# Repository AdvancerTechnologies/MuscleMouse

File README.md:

Muscle-Mouse
============

Example code and files for the Muscle Mouse project

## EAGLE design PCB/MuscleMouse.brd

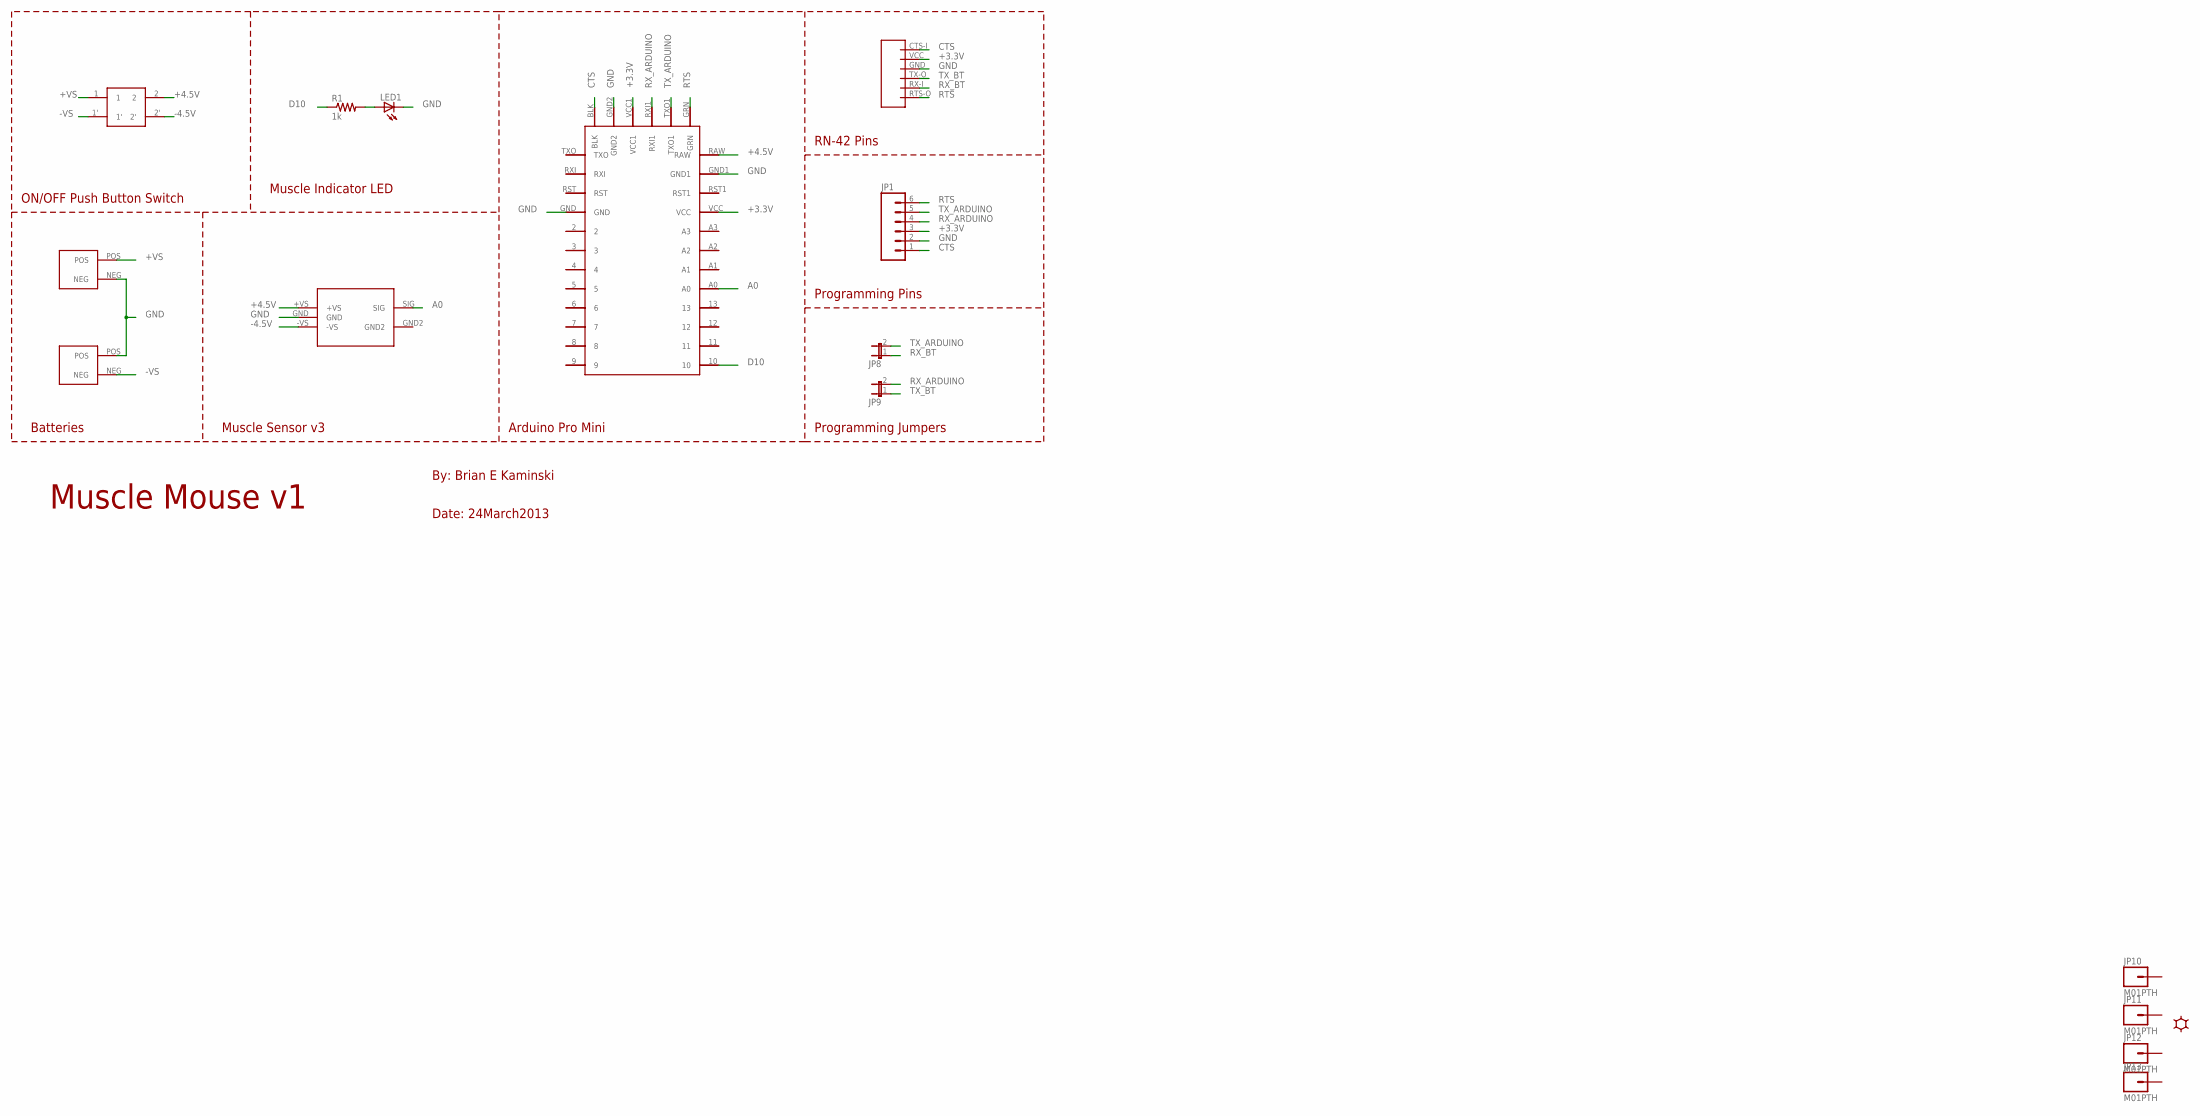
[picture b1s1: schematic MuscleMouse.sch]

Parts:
JP1: M06SIP; 1X06
JP8, JP9: JUMPER-2SMD-NC; SJ_2S
JP10, JP11, JP12, JP13: M01PTH; 1X01
LED1: LED0603; LED-0603
R1: 1k; 1206
U$1, U$2: AAA_BATT_HOLDER_3STACK
U$3: BLUESMIRF_HID
U$4: MUSCLE_SENSOR_V3
U$5: ARDUINO_PRO_MINI
U$6: ON_OFF_BUTTON
U$7: LOGOBIG; LOGO_BIG

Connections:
+3.3V: JP1.3, U$3.VCC, U$5.VCC, U$5.VCC1
+4.5V: U$4.+VS, U$5.RAW, U$6.2
+VS: U$1.POS, U$6.1
-4.5V: U$4.-VS, U$6.2'
-VS: U$2.NEG, U$6.1'
A0: U$4.SIG, U$5.A0
CTS: JP1.1, U$3.CTS-I, U$5.BLK
D10: R1.1, U$5.10
GND: JP1.2, LED1.C, U$1.NEG, U$2.POS, U$3.GND, U$4.GND, U$5.GND, U$5.GND1, U$5.GND2
unnamed: LED1.A, R1.2
RTS: JP1.6, U$3.RTS-O, U$5.GRN
RX_ARDUINO: JP1.4, JP9.2, U$5.RXI1
RX_BT: JP8.1, U$3.RX-I
TX_ARDUINO: JP1.5, JP8.2, U$5.TXO1
TX_BT: JP9.1, U$3.TX-O

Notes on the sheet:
Arduino Pro Mini
Batteries
Programming Jumpers
Muscle Sensor v3
ON/OFF Push Button Switch
Muscle Indicator LED
Programming Pins
RN-42 Pins
Muscle Mouse v1
By: Brian E Kaminski
Date: 24March2013

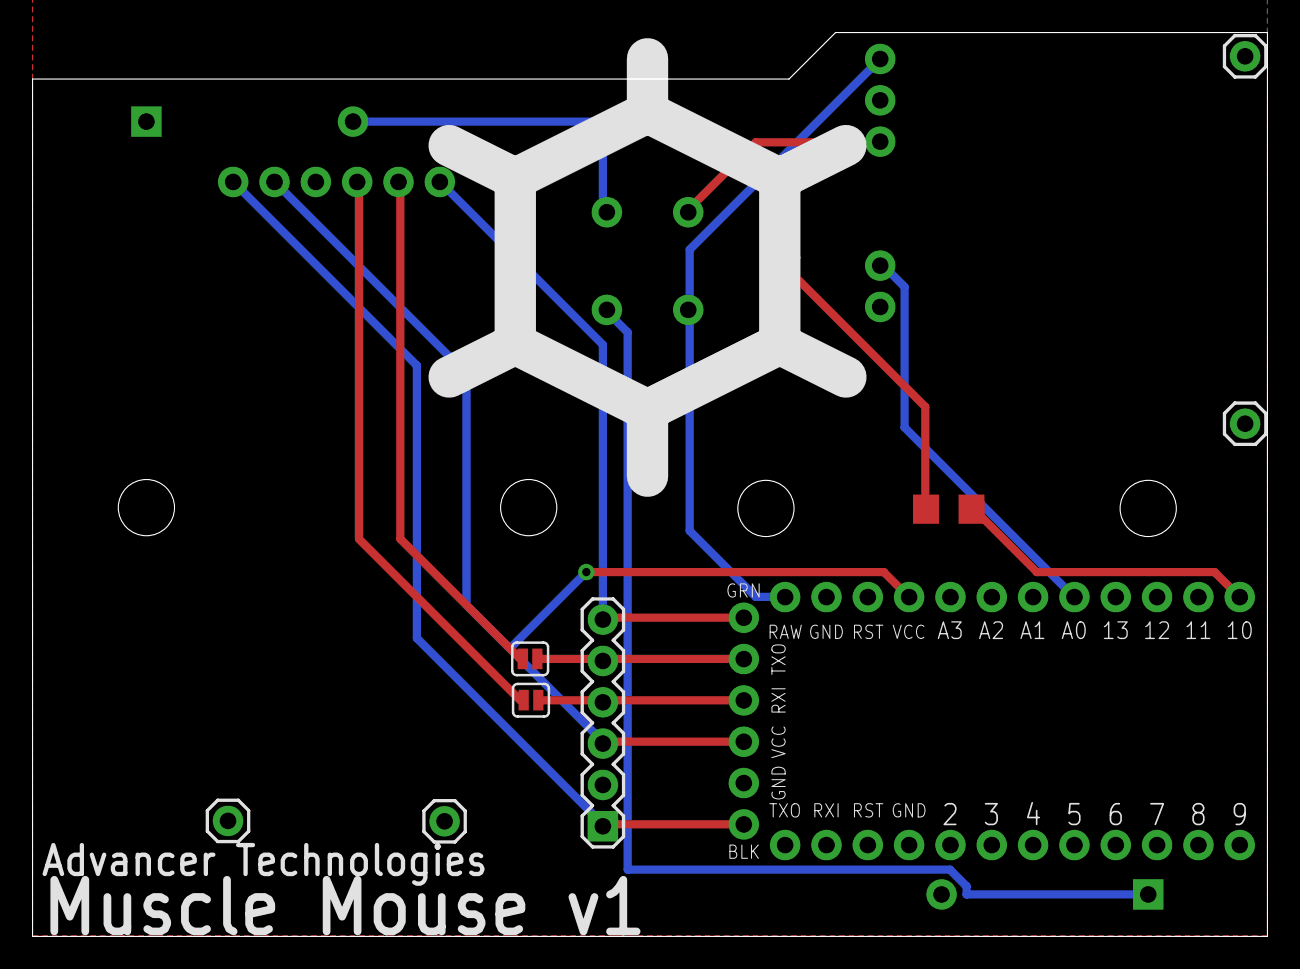
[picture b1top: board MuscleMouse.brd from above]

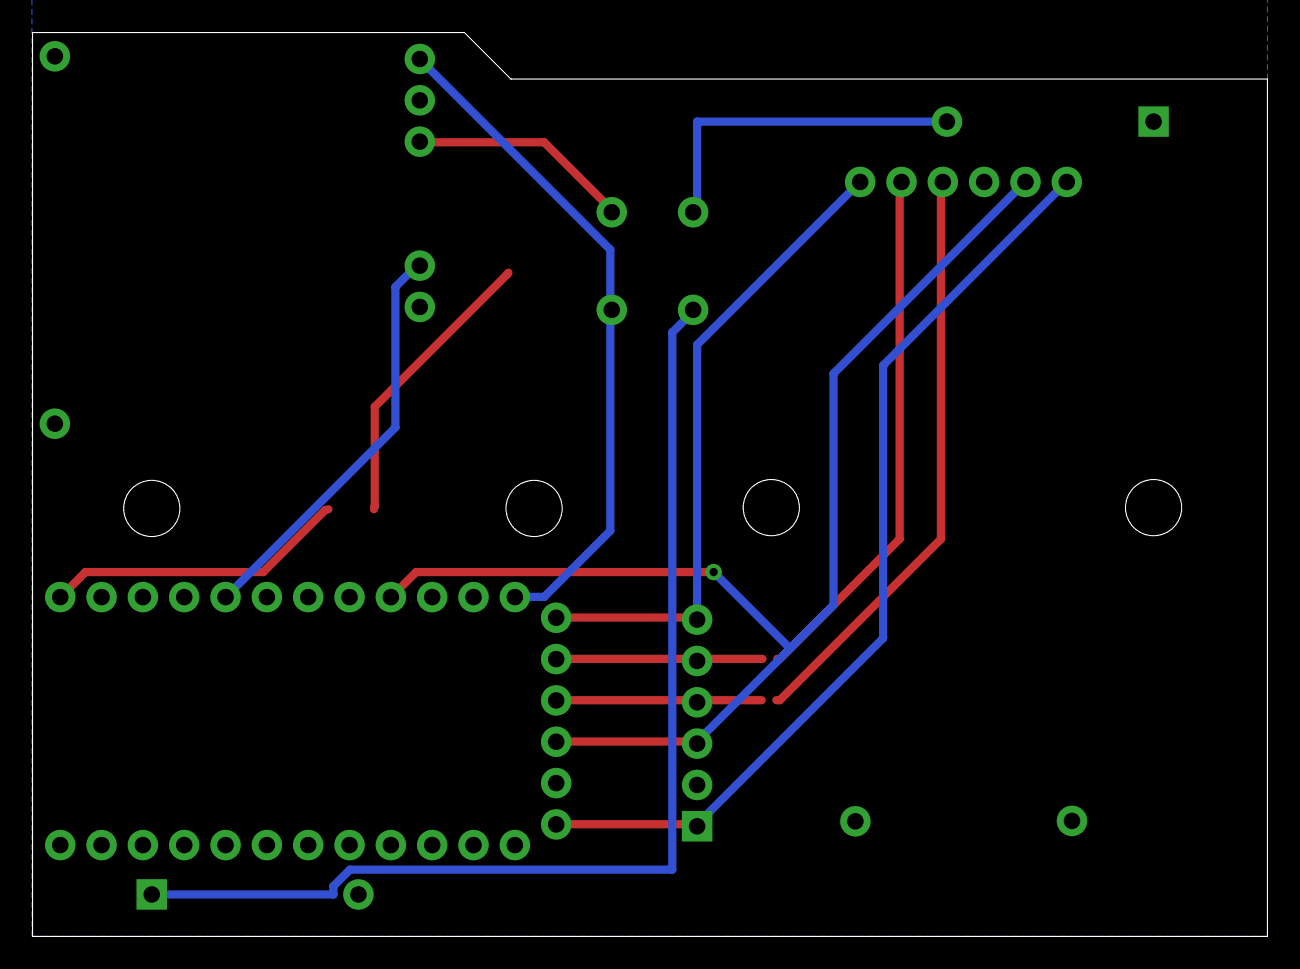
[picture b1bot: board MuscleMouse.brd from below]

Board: 2 copper layers, 75.9 x 55.5 mm, 16 parts (3 on the bottom side), 15 nets.

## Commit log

2016-07-26 RN42 Software Documentation

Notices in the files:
parts and their libraries:
SparkFun: Licensing: CC v3.0 Share-Alike You are welcome to use this library for commercial purposes.
